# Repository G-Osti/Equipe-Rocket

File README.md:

Pasta da documentação recuperada de 2022/2023 das atividades desenvolvidas na Equipe Rocket.
Não está nem um pouco organizado.

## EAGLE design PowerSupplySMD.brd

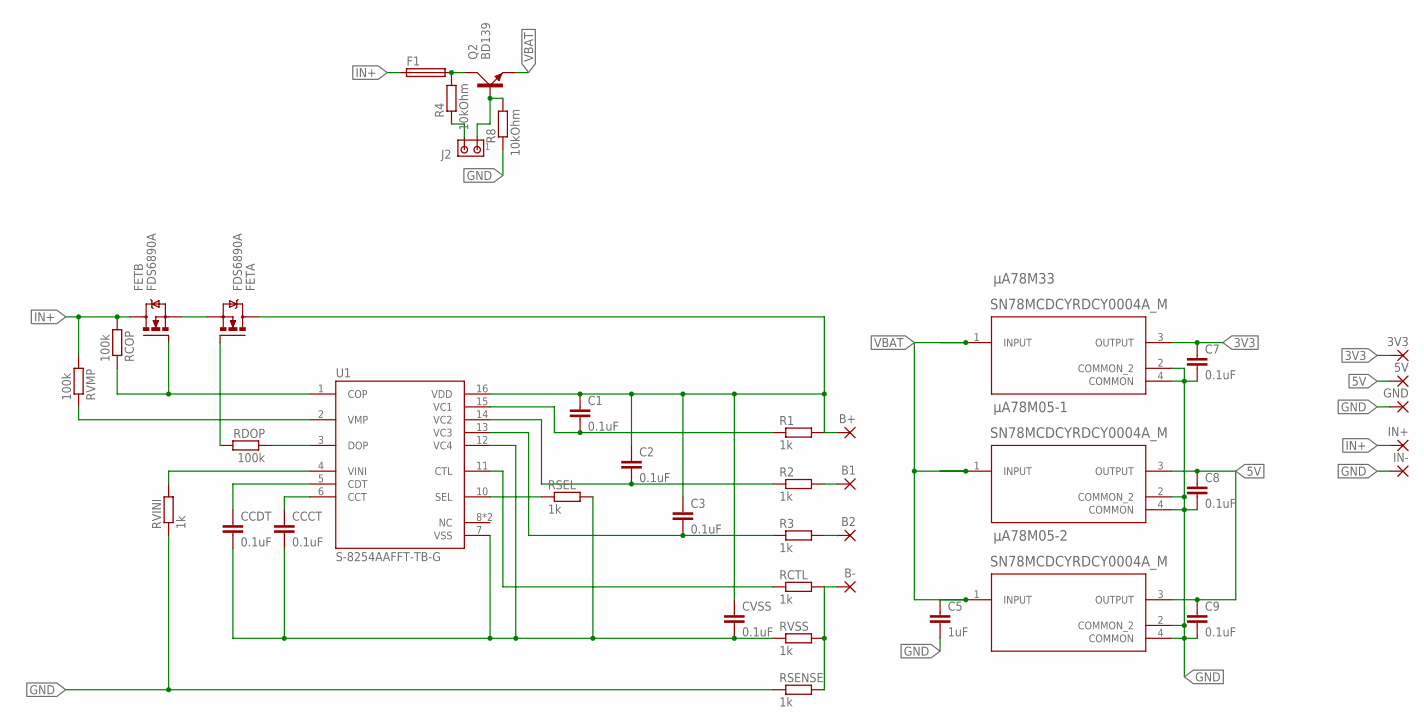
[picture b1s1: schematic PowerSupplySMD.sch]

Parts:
3V3, 5V: SMD5; SMD2,54-5,08
B1, B2: SMD5; SMD2,54-5,08
B+: SMD5; SMD2,54-5,08
B-: SMD5; SMD2,54-5,08
C1, C2, C3, C7, C8, C9: 0.1uF; C1206
C5: 1uF; C1206
CCCT: 0.1uF; C1206
CCDT: 0.1uF; C1206
CVSS: 0.1uF; C1206
F1: FUSEBLANK_5X20MM; FUSE_HOLDER_5X20MM
FET: FDS6890A; M08A
GND: SMD5; SMD2,54-5,08
IN+: SMD5; SMD2,54-5,08
IN-: SMD5; SMD2,54-5,08
J2: MTA02-100; 10X02MTA
Q2: BD139; TO126AV
R1, R2, R3: 1k; R1206
R4, R8: 10kOhm; R1206
RCOP: 100k; R1206
RCTL: 1k; R1206
RDOP: 100k; R1206
RSEL: 1k; R1206
RSENSE: 1k; R1206
RVINI: 1k; R1206
RVMP: 100k; R1206
RVSS: 1k; R1206
U1: S-8254AAFFT-TB-G; SOP65P640X110-16N
µA78M05-1, µA78M05-2, µA78M33: SN78MCDCYRDCY0004A_M; DCY0004A_M

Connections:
3V3: 3V3.1, C7.1, µA78M33.3 (OUTPUT)
5V: 5V.1, C8.1, C9.1, µA78M05-1.3 (OUTPUT), µA78M05-2.3 (OUTPUT)
B1: B1.1, R2.2
B2: B2.1, R3.2
B+: B+.1, C1.1, C2.1, C3.1, CVSS.1, FET.7 (D), FET.8 (D), R1.2, U1.16 (VDD)
B-: B-.1, RCTL.2, RSENSE.2, RVSS.2
GND: C5.2, C7.2, C8.2, C9.2, GND.1, IN-.1, R8.1, RSENSE.1, RVINI.1, µA78M05-1.2 (COMMON_2), µA78M05-1.4 (COMMON), µA78M05-2.2 (COMMON_2), µA78M05-2.4 (COMMON), µA78M33.2 (COMMON_2), µA78M33.4 (COMMON)
IN+: F1.1, FET.5 (D), FET.6 (D), IN+.1, RCOP.2, RVMP.2
unnamed: J2.2, R4.1
unnamed: J2.1, Q2.B, R8.2
unnamed: RVMP.1, U1.2 (VMP)
unnamed: FET.4 (G), RCOP.1, U1.1 (COP)
unnamed: FET.1 (S), FET.3 (S)
unnamed: RDOP.1, U1.3 (DOP)
unnamed: FET.2 (G), RDOP.2
unnamed: F1.2, Q2.C, R4.2
unnamed: C1.2, R1.1, U1.15 (VC1)
unnamed: C2.2, R2.1, U1.14 (VC2)
unnamed: C3.2, R3.1, U1.13 (VC3)
unnamed: CCCT.2, CCDT.2, CVSS.2, RSEL.2, RVSS.1, U1.7 (VSS), U1.12 (VC4)
unnamed: RCTL.1, U1.11 (CTL)
unnamed: RSEL.1, U1.10 (SEL)
unnamed: CCCT.1, U1.6 (CCT)
unnamed: CCDT.1, U1.5 (CDT)
unnamed: RVINI.2, U1.4 (VINI)
VBAT: C5.1, Q2.E, µA78M05-1.1 (INPUT), µA78M05-2.1 (INPUT), µA78M33.1 (INPUT)

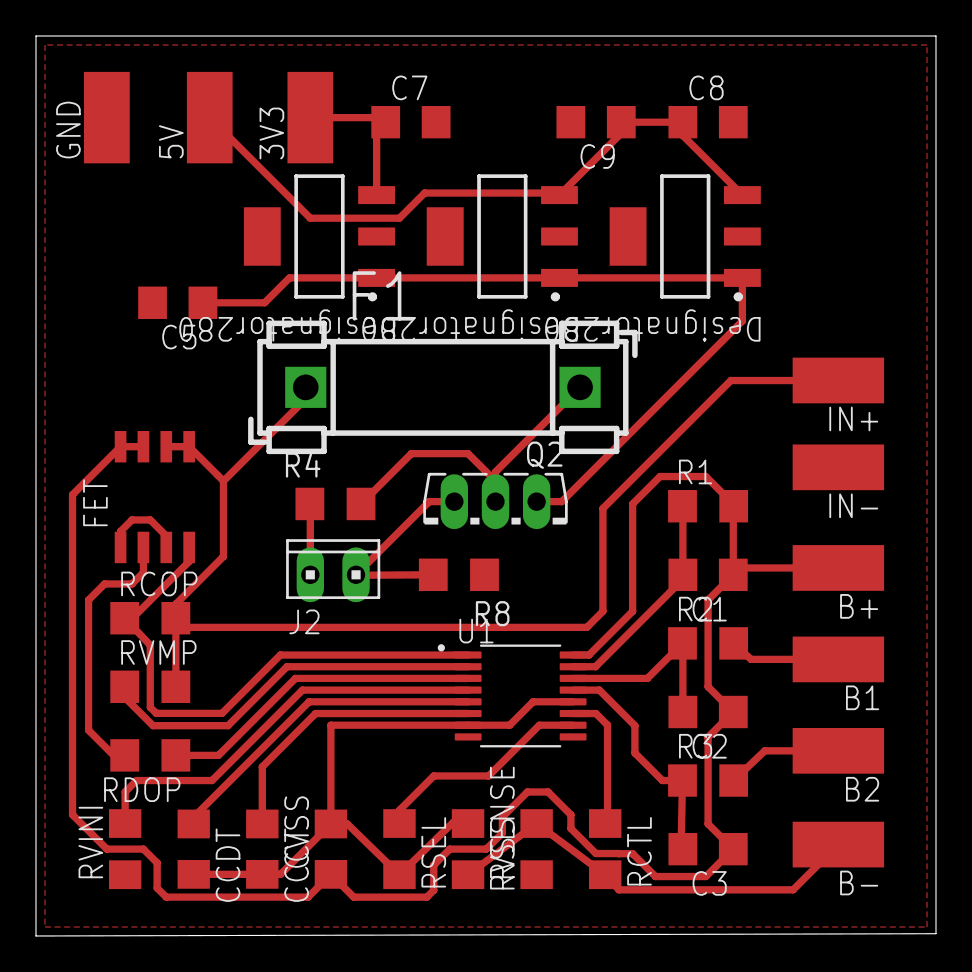
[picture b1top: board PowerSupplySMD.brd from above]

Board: 2 copper layers, 50.0 x 50.0 mm, 40 parts (0 on the bottom side), 26 nets.

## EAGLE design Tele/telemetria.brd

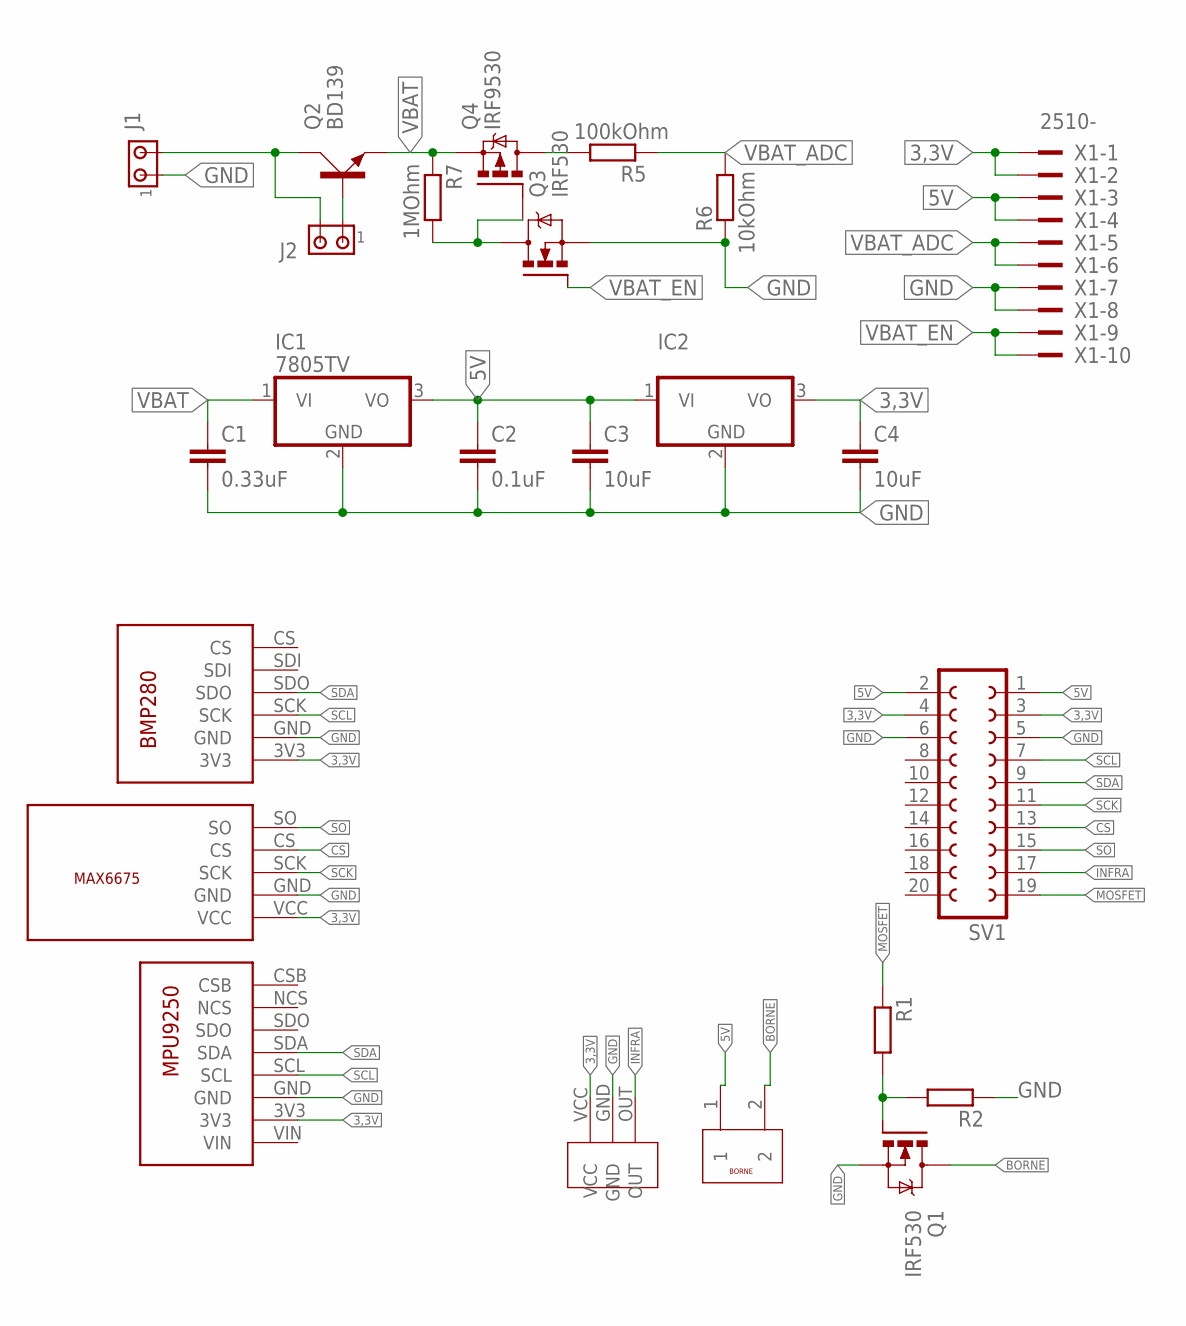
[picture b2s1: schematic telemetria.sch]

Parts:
C1: 0.33uF; C2.5-3
C2: 0.1uF; C2.5-3
C3, C4: 10uF; C2.5-3
IC1, IC2: 7805TV; TO220V
J1: MTA02-156; 1X2MTA
J2: MTA02-100; 10X02MTA
Q1, Q3: IRF530; TO220BV
Q2: BD139; TO126AV
Q4: IRF9530; TO220BV
R1: R-EU_0204/7; 0204/7
R2: R-EU_0207/10; 0207/10
R5: 100kOhm; 0207/10
R6: 10kOhm; 0207/10
R7: 1MOhm; 0207/10
SV1: FE10-2
U$1: BMP280
U$2: MAX6675
U$3: MPU9250; MP9250
U$4: PIN-INFRA
U$5: BORNE
X1: 2510-; PAK100/2500-10

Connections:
3,3V: C4.1, IC2.3 (VO), SV1.3, SV1.4, U$1.3V3, U$2.VCC, U$3.3V3, U$4.VCC, X1.1, X1.2
5V: C2.1, C3.1, IC1.3 (VO), IC2.1 (VI), SV1.1, SV1.2, U$5.1, X1.3, X1.4
BORNE: Q1.D, U$5.2
CS: SV1.13, U$2.CS
GND: C1.2, C2.2, C3.2, C4.2, IC1.2 (GND), IC2.2 (GND), J1.1, Q1.S, Q3.S, R2.1, R6.1, SV1.5, SV1.6, U$1.GND, U$2.GND, U$3.GND, U$4.GND, X1.7, X1.8
INFRA: SV1.17, U$4.OUT
MOSFET: Q1.G, R1.1, R1.2, R2.2, SV1.19
unnamed: J2.1, Q2.B
unnamed: Q4.D, R5.2
unnamed: J1.2, J2.2, Q2.C
unnamed: Q3.D, Q4.G, R7.2
SCK: SV1.11, U$2.SCK
SCL: SV1.7, U$1.SCK, U$3.SCL
SDA: SV1.9, U$1.SDO, U$3.SDA
SO: SV1.15, U$2.SO
VBAT: C1.1, IC1.1 (VI), Q2.E, Q4.S, R7.1
VBAT_ADC: R5.1, R6.2, X1.5, X1.6
VBAT_EN: Q3.G, X1.9, X1.10

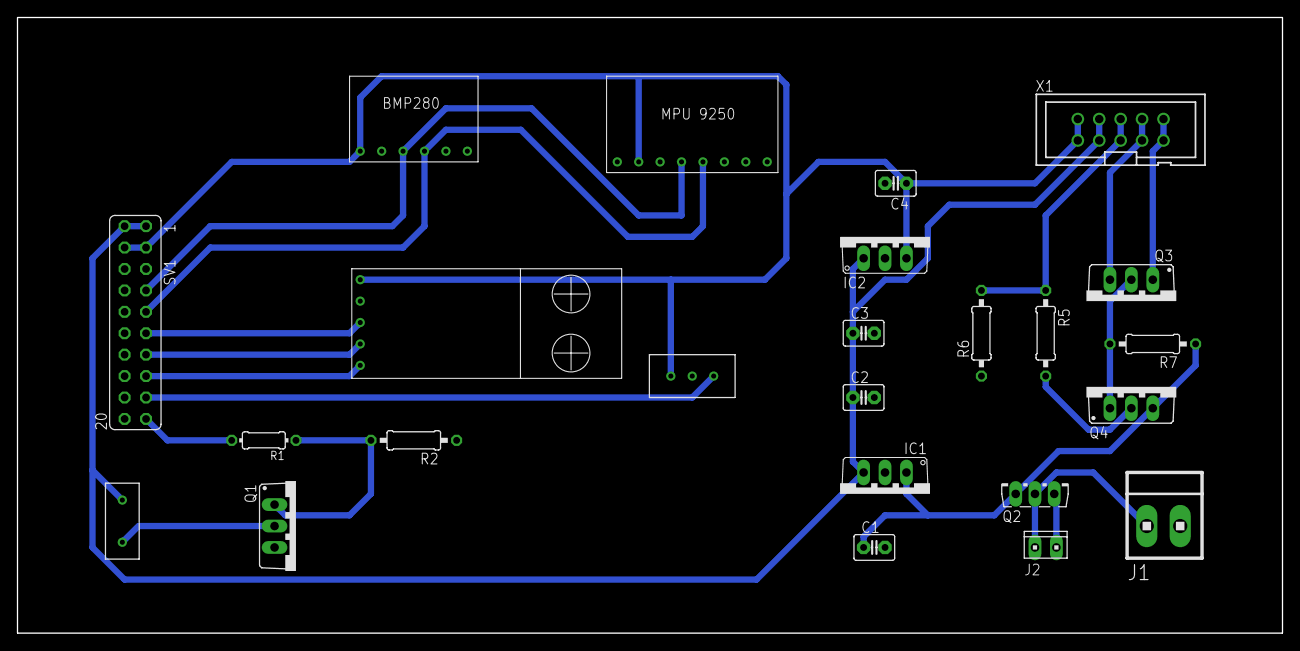
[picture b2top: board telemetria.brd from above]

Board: 2 copper layers, 150.0 x 73.0 mm, 24 parts (0 on the bottom side), 18 nets.

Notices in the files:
parts and their libraries:
COPYRIGHT: Copyright (C) 2023 Ultra Librarian. All rights reserved.
